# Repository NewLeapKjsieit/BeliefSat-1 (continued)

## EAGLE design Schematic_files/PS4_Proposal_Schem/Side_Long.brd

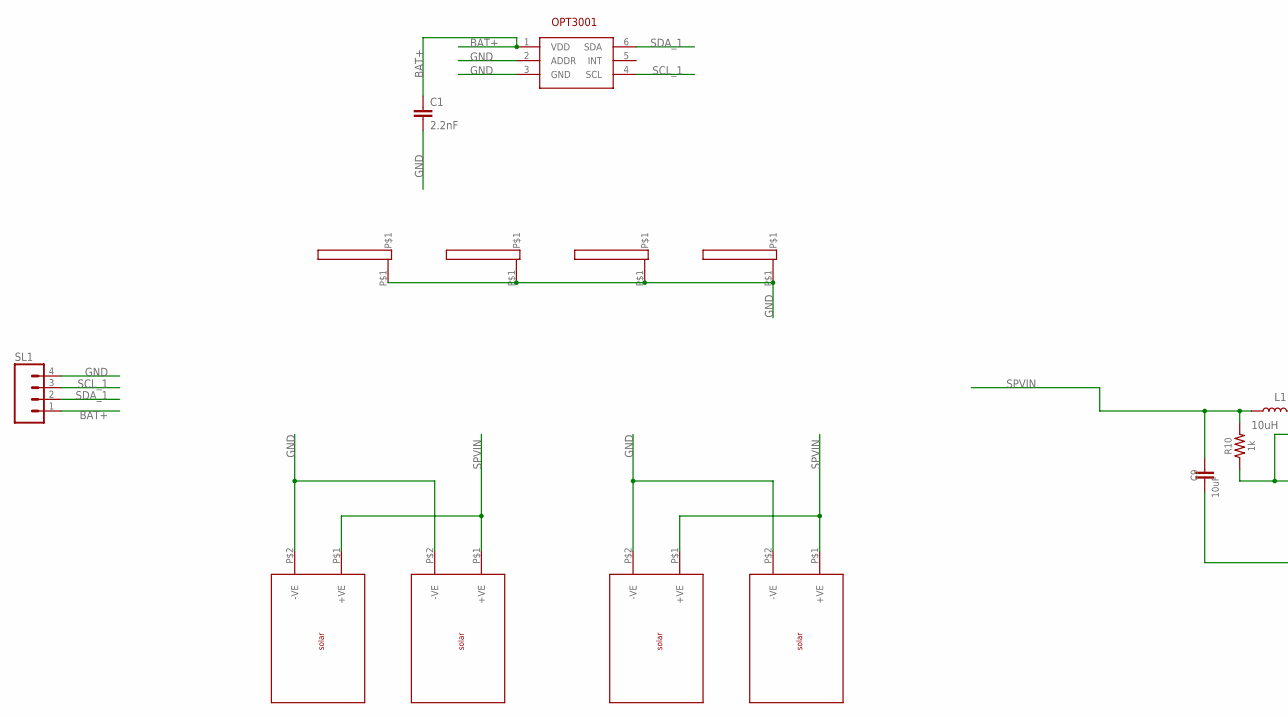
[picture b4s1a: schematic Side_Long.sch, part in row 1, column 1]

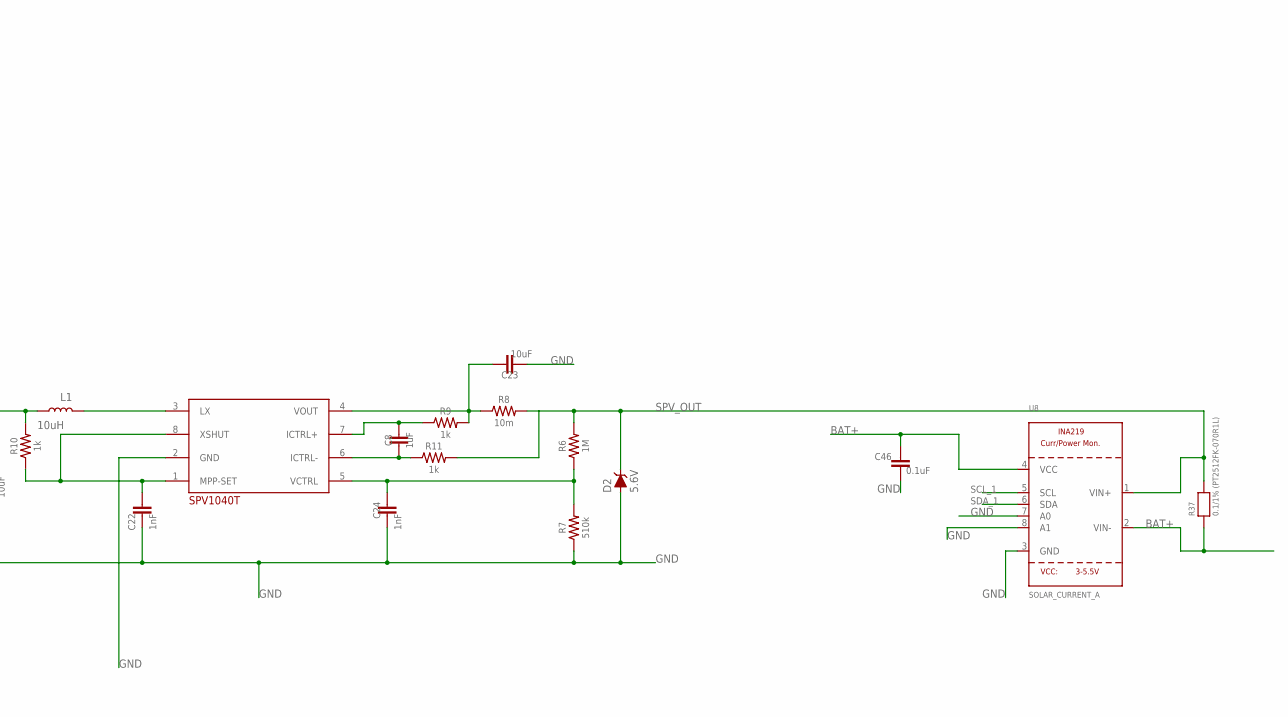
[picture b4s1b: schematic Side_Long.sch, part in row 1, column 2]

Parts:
C1: 2.2nF; 0603
C8: 1uF; 0603
C9, C23: 10uF; 0603
C22, C24: 1nF; 0603
C46: 0.1uF; 0603
D2: 5.6V; SOD-323
L1: 10uH; 0603
R6: 1M; RES_0603
R7: 510k; RES_0603
R8: 10m; RES_0603
R9, R10, R11: 1k; RES_0603
R37: 0.1/1% (PT2512FK-070R1L); 2512
SL1: M04; 04P
SPV_A: SPV1040T_; SOP65P640X120-8N
U1: SON65P200X200X65-7N
U8: SOLAR_CURRENT_A; SOT23-8
U$1, U$2, U$7, U$8: SOLAR_50_5_2; FOOT
U$3, U$4, U$5, U$6: 16X2

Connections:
BAT+: C1.1, C46.1, R37.1, SL1.1, U1.1 (VDD), U8.2 (VIN-), U8.4 (VCC)
GND: C1.2, C9.2, C22.2, C23.2, C24.2, C46.2, D2.A, R7.1, SL1.4, SPV_A.2 (GND), U1.2 (ADDR), U1.3 (GND), U8.3 (GND), U8.7 (A0), U8.8 (A1), U$1.P$2 (-VE), U$2.P$2 (-VE), U$3.P$1, U$4.P$1, U$5.P$1, U$6.P$1, U$7.P$2 (-VE), U$8.P$2 (-VE)
unnamed: L1.2, SPV_A.3 (LX)
unnamed: C22.1, R10.1, SPV_A.1 (MPP-SET), SPV_A.8 (XSHUT)
unnamed: C24.1, R6.1, R7.2, SPV_A.5 (VCTRL)
unnamed: C8.2, R11.1, SPV_A.6 (ICTRL-)
unnamed: C8.1, R9.1, SPV_A.7 (ICTRL+)
unnamed: C23.1, R8.1, R9.2, SPV_A.4 (VOUT)
SCL_1: SL1.3, U1.4 (SCL), U8.5 (SCL)
SDA_1: SL1.2, U1.6 (SDA), U8.6 (SDA)
SPVIN: C9.1, L1.1, R10.2, U$1.P$1 (+VE), U$2.P$1 (+VE), U$7.P$1 (+VE), U$8.P$1 (+VE)
SPV_OUT: D2.C, R6.2, R8.2, R11.2, R37.2, U8.1 (VIN+)

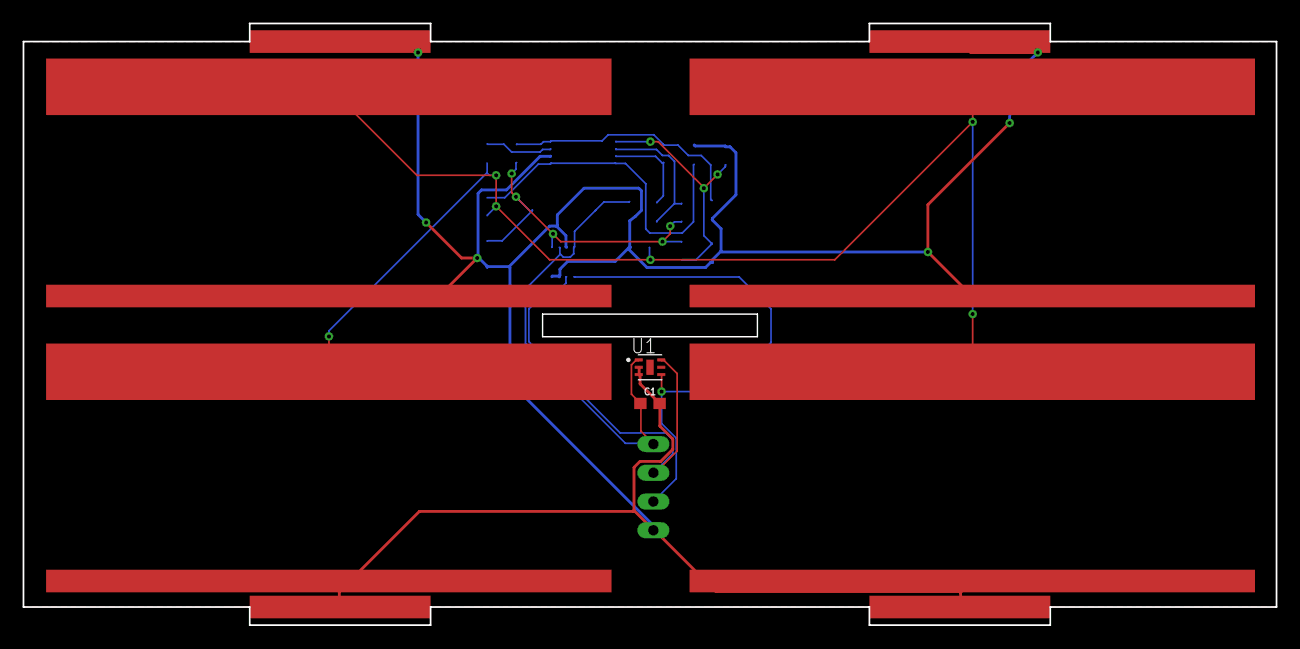
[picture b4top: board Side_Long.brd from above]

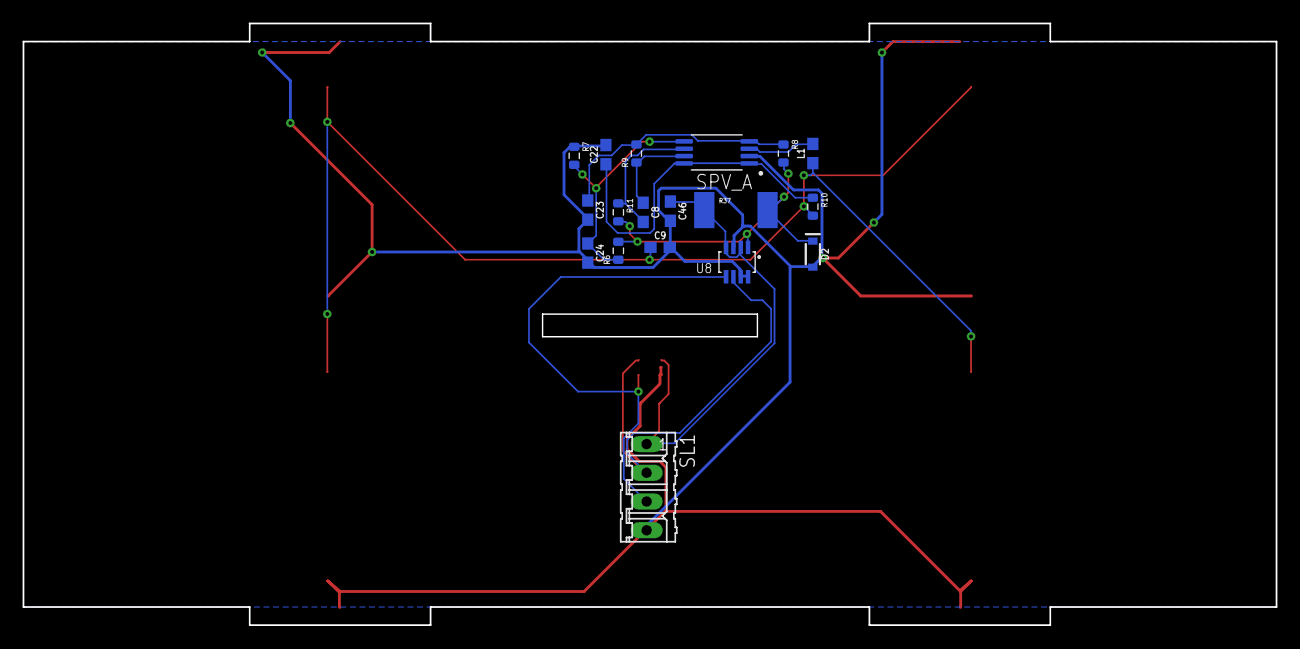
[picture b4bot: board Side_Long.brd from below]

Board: 2 copper layers, 110.8 x 53.2 mm, 28 parts (18 on the bottom side), 12 nets.
